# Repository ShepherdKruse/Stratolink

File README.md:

[stratolink.org](https://stratolink.org)

An open source pico balloon network. This repository contains the payload hardware, firmware, website, and flight models. Follow the [docs](https://stratolink.org/docs/getting-started) to build a payload, prepare a balloon, and register it on the [dashboard](https://stratolink.org/dashboard).

## Repository

```text
hardware/    KiCad schematics, PCB layouts, component libraries, and assembly files
firmware/    STM32WLE5 firmware, PlatformIO configuration, and host tests
web/         Website, public docs, dashboard, APIs, and forecast worker
supabase/    Database migrations and permission checks
simulation/  Balloon trajectories, buoyancy, and fleet coverage models
analysis/    Antenna, radio, power, and flight studies; bench diagnostics
docs/        Engineering notes for flight qualification and forecasting
scripts/     Sticker layout tool
assets/      Original project artwork and simulation media
```

## Firmware

Install [PlatformIO](https://platformio.org/install/cli). From the repository root:

```sh
cd firmware
cp include/secrets.h.example include/secrets.h
```

Fill in your regional TTN credentials, then build the flight environment:

```sh
pio run -e stratolink
```

Upload through J-Link over SWD:

```sh
pio run -e stratolink --target upload
```

Use the firmware revision that matches your board. [Hardware setup](https://stratolink.org/docs/hardware) covers assembly and programming; [firmware/README.md](firmware/README.md) covers configuration and host checks.

## Website

Use Node 22. From the repository root:

```sh
cd web
cp .env.example .env.local
ONNXRUNTIME_NODE_INSTALL=skip npm ci
npm run dev
```

Set the values in `.env.local` as described in [web/README.md](web/README.md). Run `npm run verify` before submitting website changes. Deployment and backend setup are documented there.

---

- [Fork this repository](https://github.com/Stratolink-hq/Stratolink/fork)
- [Watch this repo](https://github.com/Stratolink-hq/Stratolink/subscription)
- [Create issue](https://github.com/Stratolink-hq/Stratolink/issues/new)

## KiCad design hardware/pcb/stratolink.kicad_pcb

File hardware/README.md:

# Hardware

KiCad source files for the Stratolink payload. Follow [hardware setup](https://stratolink.org/docs/hardware) for parts, assembly, and programming.

## v1.1 downloads

- [Complete KiCad project and parts library downloads](downloads/README.md)
- [Current v1.1 board and fabrication notes](pcb/README.md)
- [Engineer reroute review and exact changes](../analysis/v1_1_engineer_review_20261015/README.md)
- [Pilot assembly BOM and placement files](gerbers/v1.1-pilot/README.md)

Download and extract the complete project, or copy the library bundle beside the matching KiCad files. The bundles include the added R24–R27, C22/C23 and U8 footprints.

## Files

- [pcb/stratolink.kicad_pro](pcb/stratolink.kicad_pro): KiCad project.
- [pcb/stratolink.kicad_sch](pcb/stratolink.kicad_sch): schematic.
- [pcb/stratolink.kicad_pcb](pcb/stratolink.kicad_pcb): board layout.
- [pcb/lib/](pcb/lib/): component symbols, footprints, and models.
- [gerbers/production_files/](gerbers/production_files/): assembly BOM and component placement exports.
- [gerbers/gerber/](gerbers/gerber/): archived drill files and drill maps.

Check the board revision before ordering parts or manufacturing boards. Generate fabrication files from the schematic and layout you have reviewed; the archived exports are not a complete fabrication package.

The [flight acceptance notes](../docs/flight/acceptance.md) cover power, RF, and assembly checks. The [hardware docs](https://stratolink.org/docs/hardware) describe the current energy-store qualification limits.

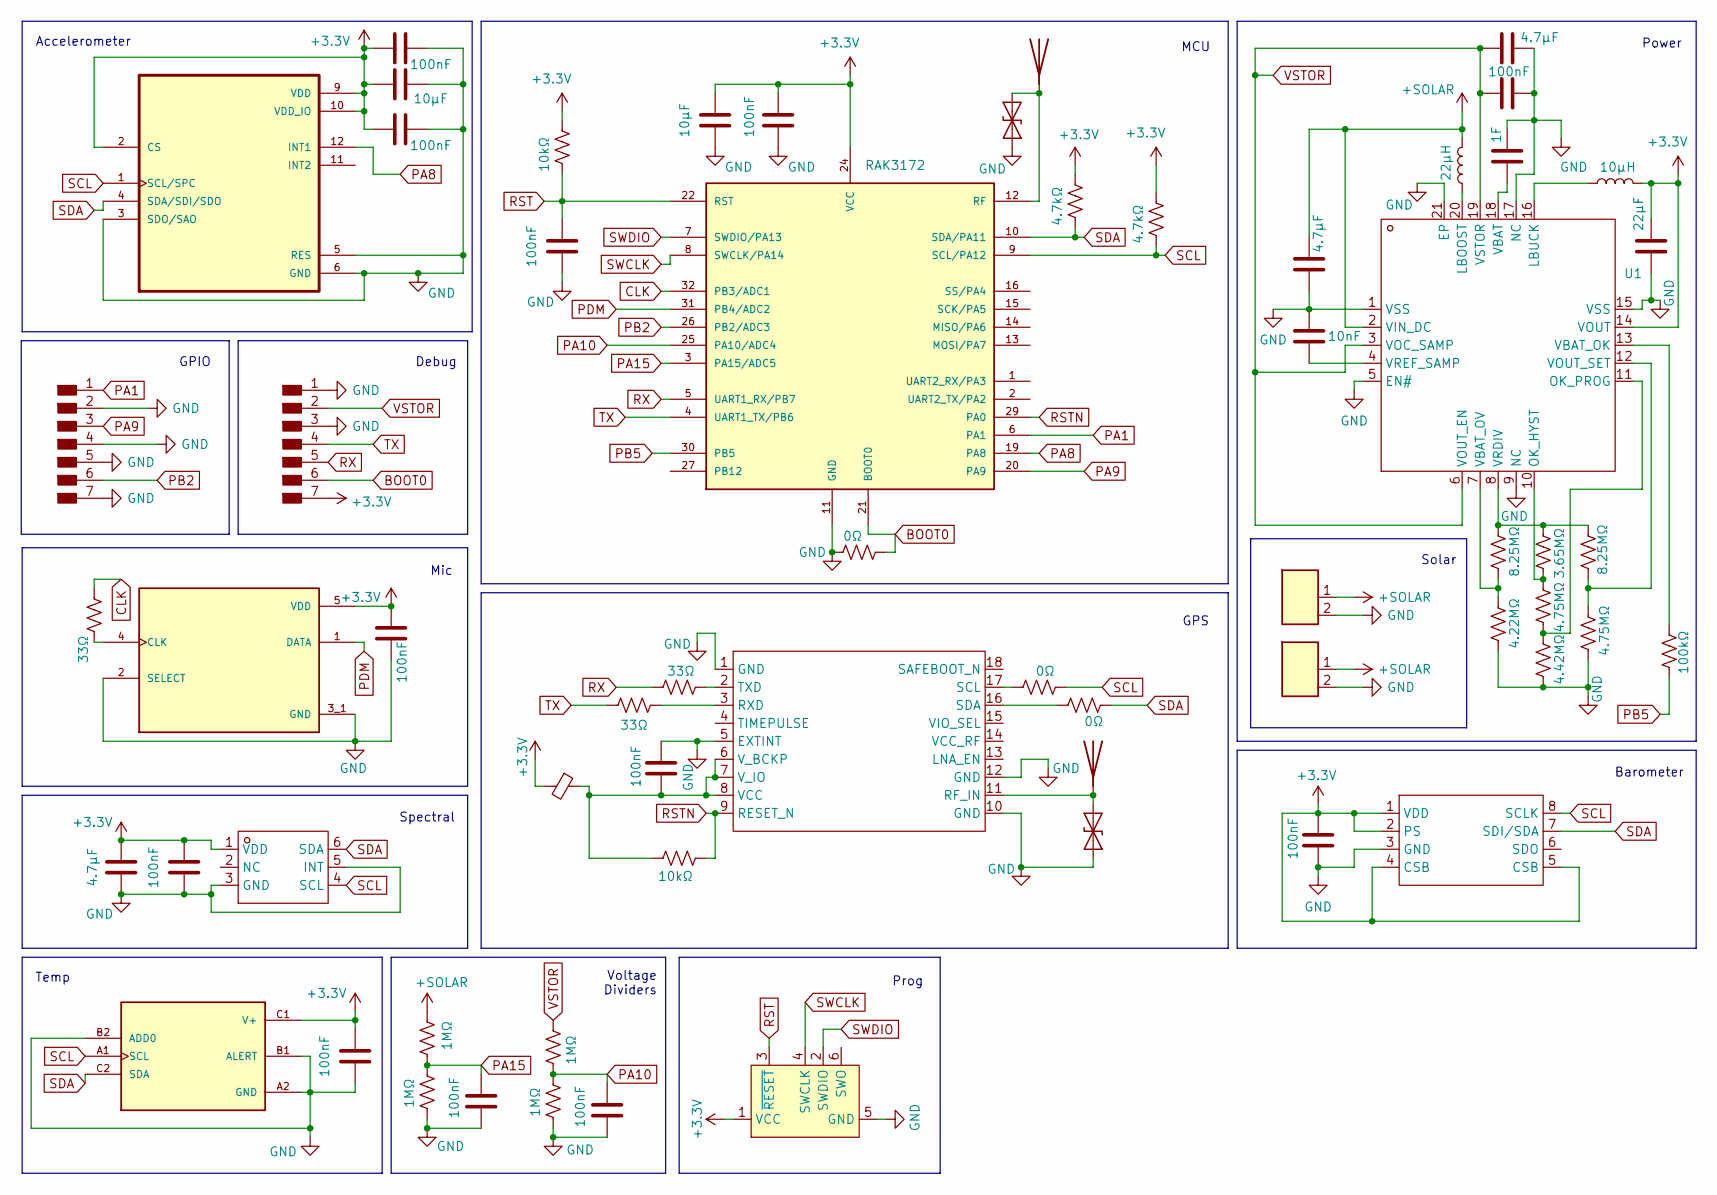
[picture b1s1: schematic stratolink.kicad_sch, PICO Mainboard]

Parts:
AE1, AE2: Antenna; 4269
C1: 10nF; C_0402_1005Metric
C2, C3, C16: 4.7μF; C_0603_1608Metric
C4, C7, C9, C10, C11, C12, C13, C14, C15, C17, C19, C20: 100nF; C_0402_1005Metric
C5: 1F; DMF4B5R5G105M3DTA0
C6: 22µF; C_0805_2012Metric
C8, C21: 10μF; C_0603_1608Metric
D1, D3: ESD9B3.3ST5G; D_SOD-523
FB1: C_0402_1005Metric
J1, J2: Conn_Header_JST_PH_1x02_P2mm_Vertical_SMD; PinHeader_1x02_P1.00mm_Vertical
J3, J4: Conn_PinHeader_1x07_P2.54mm_Vertical_THT_D1mm; PinHeader_1x07_P1.00mm_Vertical
J20: Conn_ARM_SWD_TagConnect_TC2030-NL; Tag-Connect_TC2030-IDC-NL_2x03_P1.27mm_Vertical
L1: 22µH; IND_LPS4018-223MRC
L2: 10µH; INDC1608X90N
MK1: T3902; MIC_T3902; PARTREV 1.0
R1, R6: 8.25MΩ; R_0402_1005Metric
R2: 4.22MΩ; R_0402_1005Metric
R3, R7: 4.75MΩ; R_0402_1005Metric
R4: 3.65MΩ; R_0402_1005Metric
R5: 4.42MΩ; R_0402_1005Metric
R8: 100kΩ; R_0402_1005Metric
R9, R13, R14: 0Ω; R_0402_1005Metric
R10, R18: 10kΩ; R_0402_1005Metric
R11, R12: 4.7kΩ; R_0402_1005Metric
R15, R16, R20: 33Ω; R_0402_1005Metric
R19, R21, R22, R23: 1MΩ; R_0402_1005Metric
U1: QFN50P350X350X100-21N; Manufacturer Part BQ25570RGRR; LCSC Part Name 适用于能量收集器供电应用的微功率升压充电器与降压转换器
U2: RAK3172
U3: XCVR_MAX-M10S-00B; Manufacturer Part MAX-M10S-00B; LCSC Part Name MAX-M10S-00B
U4: SON125P500X300X100-8N; Manufacturer Part MS561101BA03-50; LCSC Part Name MS561101BA03-50
U5: TMP117NAIYBGR; BGA6N40P3X2_148X95X53; PARTREV D
U6: 21-0147E; Manufacturer Part LTR-390UV-01; LCSC Part Name LTR-390UV-01 停产
U7: LIS2DH12TR; PQFN50P200X200100-12N

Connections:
+3.3V: C6.2, C7.2, C8.2, C11.2, C12.2, C13.1, C14.2, C16.2, C19.2, C20.2, C21.2, FB1.2, J4.7, J20.1 (VCC), L2.2, MK1.5 (VDD), R10.1, R11.1, R12.1, U1.14 (VOUT), U2.24 (VCC), U4.1 (VDD), U4.2 (PS), U4.4 (CSB), U4.5 (CSB), U5.C1 (V+), U6.1 (VDD), U7.2 (CS), U7.9 (VDD), U7.10 (VDD_IO)
+SOLAR: C2.1, J1.1, J2.1, L1.2, R19.1, U1.2 (VIN_DC)
BOOT0: J4.6, R9.2, U2.21 (BOOT0)
CLK: R20.2, U2.32 (PB3/ADC1)
GND: C1.1, C2.2, C3.2, C4.2, C5.2, C6.1, C7.1, C8.1, C9.1, C10.2, C11.1, C12.1, C13.2, C14.1, C15.1, C16.1, C17.1, C19.1, C20.1, C21.1, D1.1 (A1), D3.1 (A1), J1.2, J2.2, J3.2, J3.4, J3.5, J3.7, J4.1, J4.3, J20.5 (GND), MK1.2 (SELECT), MK1.3_1 (GND), MK1.3_2 (GND), R2.2, R5.2, R7.2, R9.1, R21.2, R23.2, U1.1 (VSS), U1.5 (EN#), U1.9 (NC), U1.15 (VSS), U1.17 (NC), U1.21 (EP), U1.22, U1.23, U1.24, U1.25, U1.26, U2.11 (GND), U2.17 (GND), U2.18 (GND), U2.23 (GND), U2.28 (GND), U3.1 (GND), U3.5 (EXTINT), U3.10 (GND), U3.12 (GND), U4.3 (GND), U5.A2 (GND), U5.B1 (ALERT), U5.B2 (ADD0), U6.3 (GND), U6.5 (INT), U7.3 (SDO/SAO), U7.5 (RES), U7.6 (GND), U7.7 (GND), U7.8 (GND)
unnamed: AE1.1 (A), D1.2 (A2), U2.12 (RF)
unnamed: AE2.1 (A), D3.2 (A2), U3.11 (RF_IN)
unnamed: MK1.4 (CLK), R20.1
unnamed: L1.1, U1.20 (LBOOST)
unnamed: L2.1, U1.16 (LBUCK)
unnamed: R3.1, R4.2, U1.10 (OK_HYST)
unnamed: R3.2, R5.1, U1.11 (OK_PROG)
unnamed: C5.1, U1.18 (VBAT)
unnamed: R8.1, U1.13 (VBAT_OK)
unnamed: R1.2, R2.1, U1.7 (VBAT_OV)
unnamed: R6.2, R7.1, U1.12 (VOUT_SET)
unnamed: R1.1, R4.1, R6.1, U1.8 (VRDIV)
unnamed: C1.2, U1.4 (VREF_SAMP)
unnamed: R16.2, U3.3 (RXD)
unnamed: R13.1, U3.17 (SCL)
unnamed: R14.1, U3.16 (SDA)
unnamed: R15.2, U3.2 (TXD)
unnamed: C10.1, FB1.1, R18.1, U3.6 (V_BCKP), U3.7 (V_IO), U3.8 (VCC)
PA1: J3.1, U2.6 (PA1)
PA8: U2.19 (PA8), U7.12 (INT1)
PA9: J3.3, U2.20 (PA9)
PA10: C17.2, R22.2, R23.1, U2.25 (PA10/ADC4)
PA15: C15.2, R19.2, R21.1, U2.3 (PA15/ADC5)
PB2: J3.6, U2.26 (PB2/ADC3)
PB5: R8.2, U2.30 (PB5)
PDM: MK1.1 (DATA), U2.31 (PB4/ADC2)
RST: C9.2, J20.3 (~RESET), R10.2, U2.22 (RST)
RSTN: R18.2, U2.29 (PA0), U3.9 (RESET_N)
RX: J4.5, R15.1, U2.5 (UART1_RX/PB7)
SCL: R12.2, R13.2, U2.9 (SCL/PA12), U4.8 (SCLK), U5.A1 (SCL), U6.4 (SCL), U7.1 (SCL/SPC)
SDA: R11.2, R14.2, U2.10 (SDA/PA11), U4.7 (SDI/SDA), U5.C2 (SDA), U6.6 (SDA), U7.4 (SDA/SDI/SDO)
SWCLK: J20.4 (SWCLK), U2.8 (SWCLK/PA14)
SWDIO: J20.2 (SWDIO), U2.7 (SWDIO/PA13)
TX: J4.4, R16.1, U2.4 (UART1_TX/PB6)
VSTOR: C3.1, C4.1, J4.2, R22.1, U1.3 (VOC_SAMP), U1.6 (VOUT_EN), U1.19 (VSTOR)

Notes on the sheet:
GPS
Prog
Solar
MCU
Debug
Power
Barometer
GPIO
Temp
Mic
Spectral
Voltage Dividers
Accelerometer

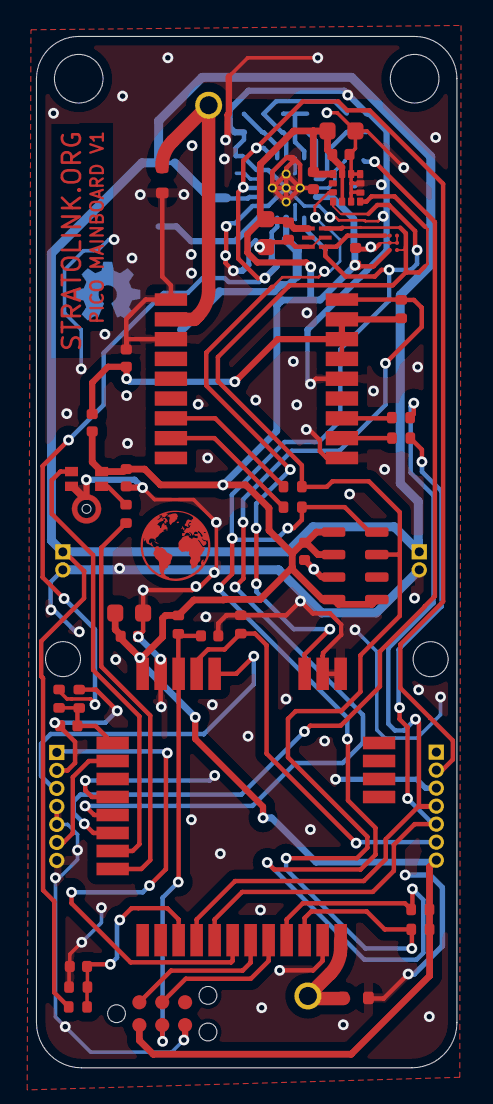
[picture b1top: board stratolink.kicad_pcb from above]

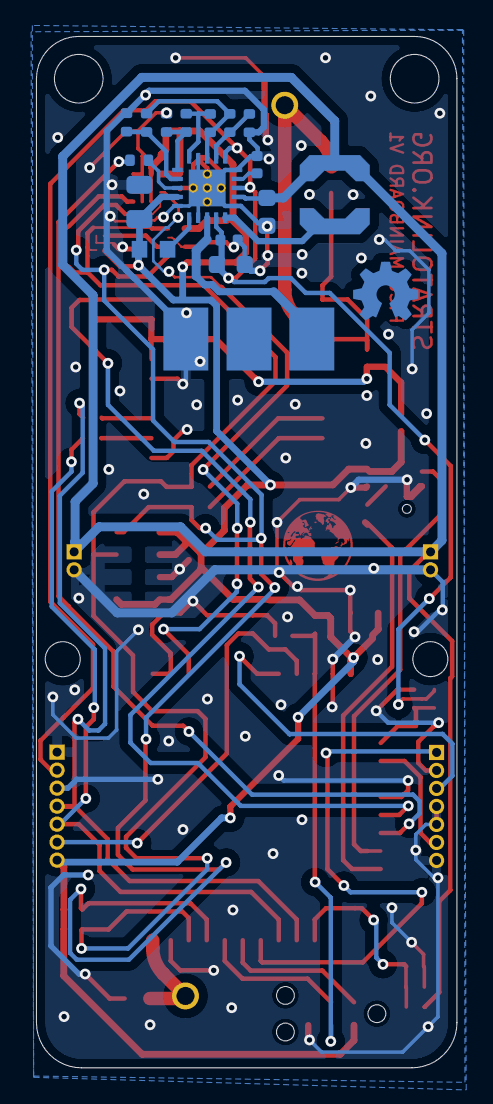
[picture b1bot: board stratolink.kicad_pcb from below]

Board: 2 copper layers, 23.4 x 57.3 mm, 62 parts (19 on the bottom side), 40 nets.

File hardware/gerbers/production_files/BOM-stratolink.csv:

Comment,Designator,Footprint,LCSC
4.7kΩ,"R11,R12",R_0402_1005Metric,C105871
0Ω,"R13,R14,R9",R_0402_1005Metric,C106231
LIS2DH12TR,U7,PQFN50P200X200100-12N,C110926
33Ω,"R15,R16,R20",R_0402_1005Metric,C138002
1MΩ,"R19,R21,R22,R23",R_0402_1005Metric,C138033
10nF,C1,C_0402_1005Metric,C3855387
100nF,"C10,C11,C12,C13,C14,C15,C17,C19,C20,C4,C7,C9",C_0402_1005Metric,C1525
~,U4,SON125P500X300X100-8N,C15639
4.7μF,"C16,C2,C3",C_0603_1608Metric,C1705
RAK3172,U2,RAK3172,C18548052
10µH,L2,INDC1608X90N,C436784
10μF,"C21,C8",C_0603_1608Metric,C19702
4.22MΩ,R2,R_0402_1005Metric,C2091474
TMP117NAIYBGR,U5,BGA6N40P3X2_148X95X53,C2871893
4.75MΩ,"R3,R7",R_0402_1005Metric,C2998153
T3902,MK1,MIC_T3902,C3171752
~,U3,XCVR_MAX-M10S-00B,C4153167
8.25MΩ,"R1,R6",R_0402_1005Metric,C423131
3.65MΩ,R4,R_0402_1005Metric,C2766827
~,U6,21-0147E,C492374
4.42MΩ,R5,R_0402_1005Metric,C49654874
~,U1,QFN50P350X350X100-21N,C506250
22µH,L1,IND_LPS4018-223MRC,C5278935
22µF,C6,C_0805_2012Metric,C602037
10kΩ,"R10,R18",R_0402_1005Metric,C60490
100kΩ,R8,R_0402_1005Metric,C60491
~,FB1,C_0402_1005Metric,C76884
ESD9B3.3ST5G,D3,D_SOD-523,C5272735
Antenna,AE2,4269,
Conn_PinHeader_1x07_P2.54mm_Vertical_THT_D1mm,J4,PinHeader_1x07_P1.00mm_Vertical,
Conn_PinHeader_1x07_P2.54mm_Vertical_THT_D1mm,J3,PinHeader_1x07_P1.00mm_Vertical,
Antenna,AE1,4269,
1F,C5,DMF4B5R5G105M3DTA0,
Conn_Header_JST_PH_1x02_P2mm_Vertical_SMD,J2,PinHeader_1x02_P1.00mm_Vertical,
Conn_Header_JST_PH_1x02_P2mm_Vertical_SMD,J1,PinHeader_1x02_P1.00mm_Vertical,

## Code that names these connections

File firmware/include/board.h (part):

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// (~30s). Draws ~3µA in backup — significant energy savings per fix.
//

// GPS UART (RAK3172 UART1 — PB6/PB7)
// Use Serial1 in Arduino framework, or the SparkFun library's serial mode.
// GPS TXD → R15 (33Ω series) → RAK3172 UART1_RX (PB7)
// GPS RXD ← R16 (33Ω series) ← RAK3172 UART1_TX (PB6)

#define GPS_SERIAL                  Serial1
#define GPS_BAUD                    9600

// GPS I2C (shared I2C bus — PA12/PA11, see I2C section)
#define GPS_I2C_ADDR                0x42

// GPS control pins
#define PIN_GPS_RESET_N             PA0   // Active-low reset, 10kΩ pullup (R18) to GPS VCC.

// GPS configuration constants
#define GPS_DYNMODEL_AIRBORNE_4G    8     // UBX-CFG-NAVSPG-DYNMODEL value
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//    I2C BUS — Shared, single pair of 4.7kΩ pull-ups (R11, R12)
// =============================================================================

#define PIN_I2C_SDA                 PA11  // Directly on RAK3172 Pin 10
#define PIN_I2C_SCL                 PA12  // Directly on RAK3172 Pin 9

// I2C Device Addresses (active on the bus)
#define I2C_ADDR_GPS                0x42  // u-blox MAX-M10S (U3) — fixed
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// dominates at ~1-3s period; gravity waves are 5-30 min period, so they're
// easily separable with a low-pass filter.

#define PIN_ACCEL_INT1              PA8   // LIS2DH12 INT1 output.
                                          // Configure as EXTI wakeup source for
                                          // freefall → burst detection.
                                          // Rising edge = interrupt active.
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// library or equivalent CIC filter).
//
// SPI1 alternate function mapping (AF5):
//   PB3 = SPI1_SCK  → drives mic CLK (through 33Ω series resistor)
//   PB4 = SPI1_MISO → receives mic PDM DATA (direct connection)
// This allows hardware SPI in receive-only master mode — no bit-banging needed.
//
// Power modes:
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//   - Off:    remove VDD via power gating = 0 µA
// Wake-up from sleep: 32,768 SCK clock cycles (~13.6 ms at 2.4 MHz).

#define PIN_MIC_PDM_CLK             PB3   // SPI1_SCK (AF5). Clock output to T3902.
                                          // 33Ω series resistor between MCU and mic.

#define PIN_MIC_PDM_DATA            PB4   // SPI1_MISO (AF5). PDM data input from T3902.
                                          // Direct connection, no series resistor.

#define MIC_PDM_CLOCK_HZ            2400000  // ~2.4 MHz nominal
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// Solar cells → VIN_DC → boost charger → VSTOR (supercap) → buck → VOUT (3.3V)

// --- VBAT_OK: power-good flag from BQ25570 ---
#define PIN_VBAT_OK                 PB5   // Digital input. Active high.
                                          // Connected through R8 (100kΩ series) to
                                          // BQ25570 VBAT_OK output (U1 pin 13).
                                          // HIGH = supercap above ~3.51V (rising)
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// GPIO to analog mode, wait, then read. Do NOT rely on default sampling
// time — it's far too short for this impedance.

#define PIN_VSTOR_ADC               PA10  // ADC channel 4 (ADC_IN4)
#define VSTOR_DIVIDER_RATIO         2.0f  // Multiply ADC voltage by this
#define VSTOR_DIVIDER_R_TOP         1000000  // R22, 1MΩ
#define VSTOR_DIVIDER_R_BOT         1000000  // R23, 1MΩ
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//
// Same high source impedance as VSTOR — same 50 ms settling requirement.

#define PIN_SOLAR_ADC               PA15  // ADC channel 5 (ADC_IN5)
#define SOLAR_DIVIDER_RATIO         2.0f  // Multiply ADC voltage by this
#define SOLAR_DIVIDER_R_TOP         1000000  // R19, 1MΩ
#define SOLAR_DIVIDER_R_BOT         1000000  // R21, 1MΩ
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// 10. SPARE GPIOs — Available on J3 header
// =============================================================================

#define PIN_SPARE_PA1               PA1   // Spare GPIO
#define PIN_SPARE_PA9               PA9   // Spare GPIO
#define PIN_SPARE_PB2               PB2   // Spare GPIO

// =============================================================================
// 11. SWD DEBUG INTERFACE
// =============================================================================

#define PIN_SWDIO                   PA13  // SWD data — directly on RAK3172 Pin 7
#define PIN_SWCLK                   PA14  // SWD clock — directly on RAK3172 Pin 8

// =============================================================================
// 12. BOARD METADATA
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
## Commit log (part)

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2026-05-30 Radically simplify the map
2026-05-30 Simplify mobile
2026-05-30 Add secure RLS migration and use devices_public
    Lock down permissive Supabase write policies and add a safe devices_public view (migration 010) for public dashboard reads. Update server and client code to use devices_public instead of the base dev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
2026-05-30 Create a swiss simple style
2026-05-30 Bathymetry map style
2026-05-30 More realistic day/night gradient
2026-05-31 Compute payload attitude; refine telemetry metrics
    Add payload attitude computation and use it in TelemetryV3Panel: introduce PayloadAttitude type and computePayloadAttitude in flightSeries.ts, remove legacy tilt/sway from FlightSeries, and wire the 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
2026-05-31 Fix payload attitude axis handling and UI copy
    Correct computePayloadAttitude to treat +Y as the vertical axis and X/Z as the horizontal (swing) plane: horizontal = hypot(ax, az), total = hypot(ax, ay, az), tilt uses ay as the vertical component.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
2026-05-31 Add dashboard theme support and toggle
    Introduce a DashboardThemeProvider and useDashboardTheme hook (persisted to localStorage) and a ThemeToggle button. Wire the provider into the dashboard layout and propagate the selected theme to Mis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
2026-05-31 Make terminator theme-aware and add header logo
    Teach the day/night terminator to respect the map color scheme and strengthen contrast on dark basemaps: DayNightTerminator now accepts a colorScheme prop and adjusts raster opacity; TerminatorSource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
2026-05-31 Add event timeline and map time-pick
    Introduce an interactive EventTimeline component and supporting flightNarrative utility to detect flight milestones, build narrative segments (gaps/signals), and map between time and rail fraction. I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
2026-05-31 Replace EventTimeline with Timeline
    Remove the EventTimeline component and update MissionControl to use the new Timeline component. Call sites in MissionControl were updated to pass visibleRows and futureEndT (replacing rows and launch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
2026-05-31 Simplify the sidebar charts
2026-05-31 Couple of small tweaks
2026-05-31 Remove bands from temperature panel
2026-05-31 Fix mobile
2026-05-31 Improve dark mode and mobile globe centering
2026-05-31 Black marble dark mode
2026-05-31 Fix scrubber time alignment
2026-05-31 Break gateway connections in no tx zones
2026-05-31 tx dots always on
2026-05-31 dark mode improvements
2026-05-31 Show estimated paths
2026-05-31 [DOC] removed old firmware extention section
2026-05-31 Add black marble lights to night side of globe
2026-05-31 Improve night lights and shadow behavior
2026-06-01 Safety net: compute inline on a cold-cache miss
    The read-only forecast path left prod stuck at 202 forever — it only ever
    returns the forecast from cache, so when the cache can't be served/persisted
    (e.g. Vercel Blob not writable) the client never gets one. The old code masked
    this by returning the freshly-computed forecast inline.
    Restore that for the cold-miss case only: compute inline and return it (200),
    best-effort caching for the next reader; a concurrent in-flight compute returns
2026-06-01 I don't know how this got overwritten?
2026-06-01 Use private Blob access so the forecast/hindcast cache persists
    The store is a PRIVATE Vercel Blob store, but storeForecast/storeHindcast wrote
    with access:'public', which the store rejects ("Cannot use public access on a
    private store") — so every cache write failed and nothing was ever stored.
    Upgrade @vercel/blob 0.27 → 2.4 (which supports private blobs) and switch
    writes to access:'private' and reads to the authenticated get() (token from
    env) instead of a public-URL fetch. Verified with a private put+get round-trip
2026-06-01 Center uncertainty ellipses on the path, across both legs
    The ellipses were centered on the ensemble mean, which over a multi-day
    dead-reckon drifts ~1000-1600 km from the nominal path — so they floated off,
    disconnected from the line. Now:
    - The ensemble runs as full trajectories (fix → now → horizon), so the cloud
    exists for the predicted hindcast leg too, not just the forecast.
    - Each 50/90% ellipse is sliced across the whole path and RE-CENTERED on the
2026-06-02 [BUG] firmware: gate GPS on fresh PVT, PA0-reset a wedged module
2026-06-02 [FEAT] firmware: GPS bench diagnostics (gps_diag, gps_diag2, gps_iprobe)
2026-06-02 [DOC] firmware: correct stale README/DOCUMENTATION (sleep tiers, GPS freshness, region/session, STOP2)
2026-06-03 terminator scrubbing and mobile fixes
2026-06-03 show last contact in days - hours when greater than 24 hours
2026-06-03 [FEAT] firmware: pin uplink SF9, 1200s cadence (+ SF9 safety guards)
    Uplink SF 7->9 in all four region tables (lorawan.cpp). SF9 buys +5 dB
    sensitivity, ~2x link-budget range, which clears the 412 km radio horizon
    at float. Flight-1 ran at the SF7 floor; the antenna study (analysis/
    antenna) showed the flown antenna was good (2.7 dBi, matched), so the
    deficit is the link budget, not the antenna. Join SF is unchanged
    (SF10 US/AU, SF7 EU/AS), flight-proven; only uplinks move.
2026-06-03 Fetch only new points from supabase
2026-06-03 [DOC] firmware: correct stale sleep-tier comment (power_adc.h)
2026-06-03 [FIX] firmware: drop dead reset-cycle fallback, correct IWDG-in-Stop comments
2026-06-03 [FIX] firmware: mic detector uses DC-blocked variance, not fixed-centre RMS
2026-06-03 [FEAT] analysis: mic bench rig (J-Link PDM capture) + acoustic flight audit
2026-06-03 No longer compute speed and direction bias from previous samples. Too noisy
2026-06-04 [FEAT] analysis: TTN/Meshtastic relay study, power/duty models + SDR/coverage figures
2026-06-04 [FEAT] firmware: power-gated Meshtastic open-relay on the shared SX1262
2026-06-04 [DOC] analysis: phase-2 final report (TTN+Meshtastic 18.3h soak, models, results)
2026-06-15 feat: update dependencies to latest versions
